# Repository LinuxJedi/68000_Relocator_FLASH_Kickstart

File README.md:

# 68000 Relocator with FLASH based Kickstart
Forked from https://github.com/PR77/68000_Relocator_FLASH_Kickstart and the software and firmware have been modified as well as a GUI tool created.

It now supports two flashed kickstart ROMs and has a cleaner interface.

**NOTE:** If you are using FK 3.0 command line tool or FlashKickstart GUI tool you will need to use the 3.0 Xilinx firmware too. Otherwise hi/lo ROMs will be the mapped to the same address.

**NOTE 2:** With firmware version 3.4 onwards the the jumper now switches between motherboard and ROM bank 1 as the first ROM. Jumper off for motherboard, jumper on for board ROM1. You will need 39SF040 ROM chips to use 3.4 onwards.

**NOTE 3:** The hardware directory in this tree was a PoC and will not work. Please use PR77's board linked to in the GitHub link above.

# Overview
To allow for Flash Kickstart images to be mapped in the same address space as existing ROM Kickstart without the need to remove the existing ROM. This design is targeting an accelerated A500(+) system which also require a CPU relocation.

# Flashing new ROMs
It is recommended you use the included FlashKickstart GUI tool. To use this you may need to install the reqtools library in your LIBS: drive. If you are using Kickstart 1.3 this is available in the lib13 directory of the software, for 2.0 onwards use the version in libs20 directory.

You can then load "FlashKickstart" and you should see the window similar to below:

You need to erase the ROMs before flashing a new image. Erasing will clear both the flash ROM slots.

You can then program with any ROM you wish. You should not use byte-swapped ROMs.

# Using the ROMs
In principle the operation is fairly simple. A CPLD is used to switch between the ROM Kickstart on the Motherboard or the two Flash Kickstart on the CPU Relocator. Switching is performed by an active /RESET (CTRL-A-A) without interruption for longer than 1 second. Shorter /RESET durations will simply just reset the Amiga. After a POR (Power On Reset) by default the Kickstart on the Motherboard will be used.

## ROM based Kickstart
When ROM Kickstart is being used, the hardware simply passed /AS to the Amiga Motherboard to allow GARY perform the address decode and chip select of the internal ROM. During this process, the Flash Kickstart is simply not used - except when programming. A Zorro II space of 1MB is requested and allocated by the Amiga which maps to the Flash devices.

When programming the Flash devices, access is via this Zorro II space. Programming of the Flash devices can only be performed when ROM Kickstart is being used.

## FLASH based Kickstart
When Flash Kickstart is being used, the hardware simply blocks /AS to the Amiga Motherboard and the CPLD will perform the operation of Flash device control. As /AS is not asserted on the Amiga Motherboard, and therefore no GARY decode, the Relocator CPLD will then also assert the /DTACK after placing data on the bus - this is needed to complete the CPU cycle.

### Overlay Interception
When Flash Kickstart mode is being used, the CPLD will also intercept the overlay of the Kickstart in the 0x000000 memory space until the first access to the custom chip register is performed. This ensures the correct SP and IP initialisation is performed directly after POR (Power On Reset) as the Flash Kickstart is used by default.

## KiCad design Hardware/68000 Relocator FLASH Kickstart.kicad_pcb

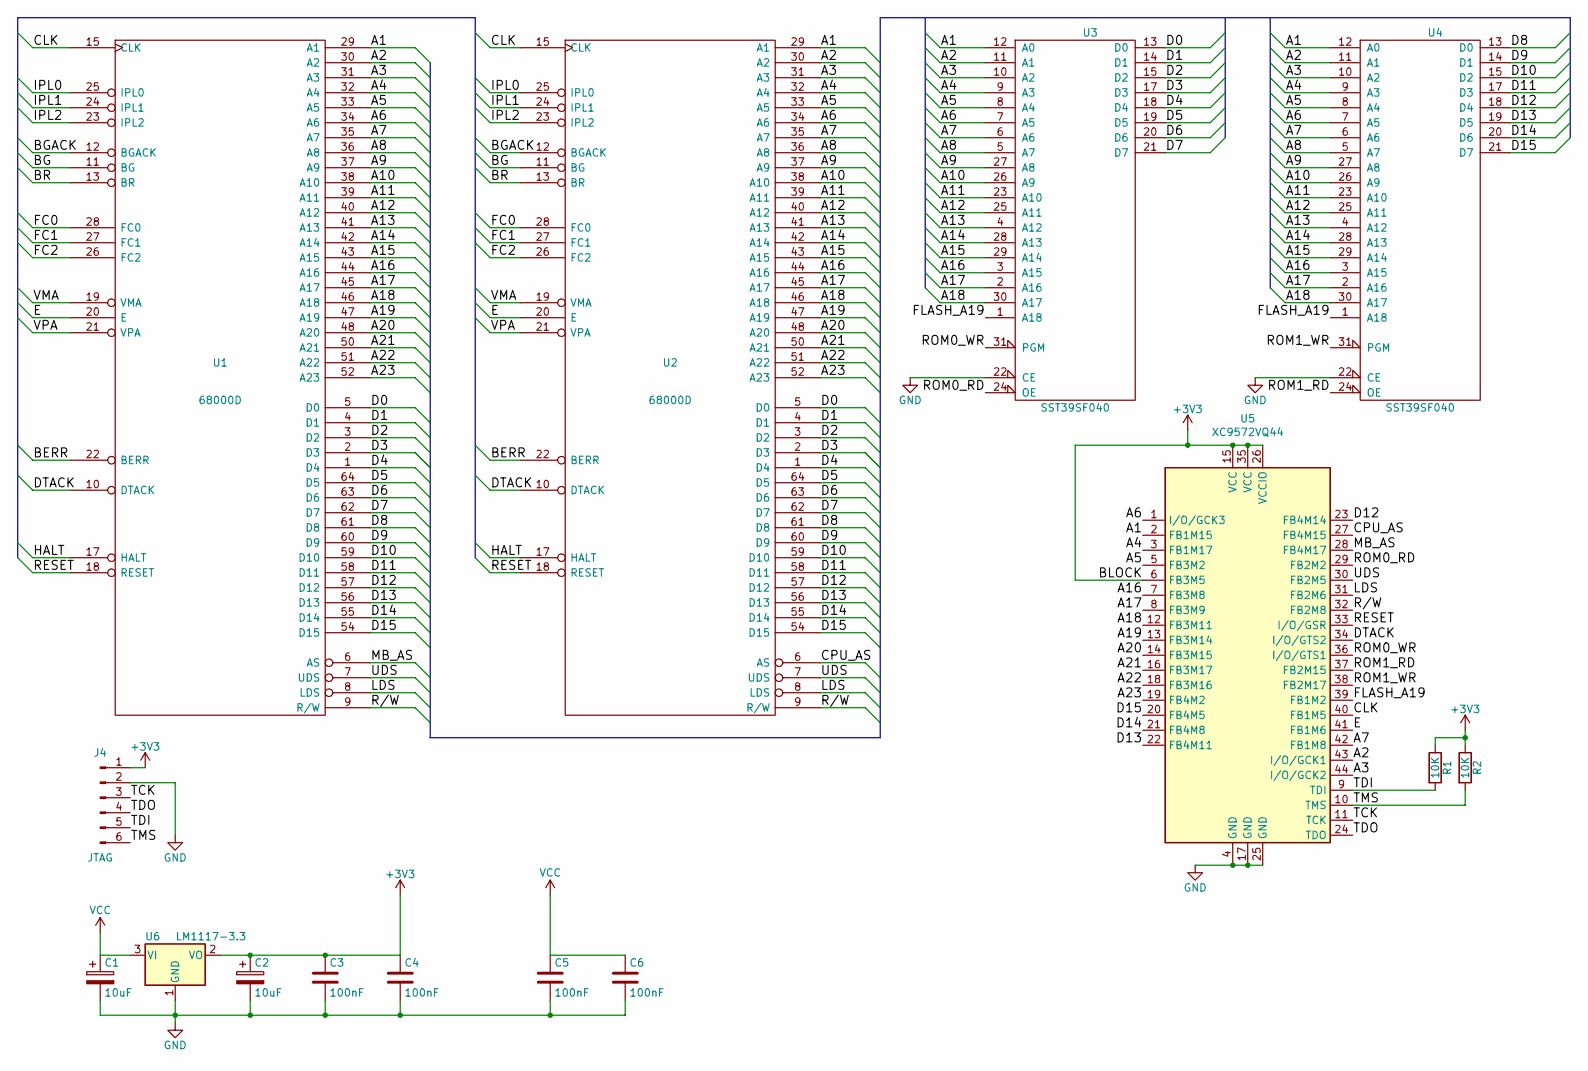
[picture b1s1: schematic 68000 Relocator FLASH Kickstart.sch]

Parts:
C1, C2: 10uF; CP_Tantalum_Case-B_EIA-3528-21_Hand
C3, C4, C5, C6: 100nF; C_0805_HandSoldering
J4: JTAG; Pin_Header_Straight_1x06_Pitch2.54mm
R1, R2: 10K; R_0805_HandSoldering
U1, U2: 68000D; DIP-64_W22.86mm_Socket_LongPads
U3, U4: SST39SF040; DIP-32_W15.24mm_Socket
U5: XC9572VQ44; TQFP-44_10x10mm_Pitch0.8mm
U6: LM1117-3.3; SOT-223-3_TabPin2

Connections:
+3V3: C2.1, C3.1, C4.1, J4.1, R1.1, R2.1, U5.6 (FB3M5), U5.15 (VCC), U5.26 (VCCIO), U5.35 (VCC), U6.2 (VO)
/A1: U1.29 (A1), U2.29 (A1), U3.12 (A0), U4.12 (A0), U5.2 (FB1M15)
/A2: U1.30 (A2), U2.30 (A2), U3.11 (A1), U4.11 (A1), U5.43 (I/O/GCK1)
/A3: U1.31 (A3), U2.31 (A3), U3.10 (A2), U4.10 (A2), U5.44 (I/O/GCK2)
/A4: U1.32 (A4), U2.32 (A4), U3.9 (A3), U4.9 (A3), U5.3 (FB1M17)
/A5: U1.33 (A5), U2.33 (A5), U3.8 (A4), U4.8 (A4), U5.5 (FB3M2)
/A6: U1.34 (A6), U2.34 (A6), U3.7 (A5), U4.7 (A5), U5.1 (I/O/GCK3)
/A7: U1.35 (A7), U2.35 (A7), U3.6 (A6), U4.6 (A6), U5.42 (FB1M8)
/A8: U1.36 (A8), U2.36 (A8), U3.5 (A7), U4.5 (A7)
/A9: U1.37 (A9), U2.37 (A9), U3.27 (A8), U4.27 (A8)
/A10: U1.38 (A10), U2.38 (A10), U3.26 (A9), U4.26 (A9)
/A11: U1.39 (A11), U2.39 (A11), U3.23 (A10), U4.23 (A10)
/A12: U1.40 (A12), U2.40 (A12), U3.25 (A11), U4.25 (A11)
/A13: U1.41 (A13), U2.41 (A13), U3.4 (A12), U4.4 (A12)
/A14: U1.42 (A14), U2.42 (A14), U3.28 (A13), U4.28 (A13)
/A15: U1.43 (A15), U2.43 (A15), U3.29 (A14), U4.29 (A14)
/A16: U1.44 (A16), U2.44 (A16), U3.3 (A15), U4.3 (A15), U5.7 (FB3M8)
/A17: U1.45 (A17), U2.45 (A17), U3.2 (A16), U4.2 (A16), U5.8 (FB3M9)
/A18: U1.46 (A18), U2.46 (A18), U3.30 (A17), U4.30 (A17), U5.12 (FB3M11)
/A19: U1.47 (A19), U2.47 (A19), U5.13 (FB3M14)
/A20: U1.48 (A20), U2.48 (A20), U5.14 (FB3M15)
/A21: U1.50 (A21), U2.50 (A21), U5.16 (FB3M17)
/A22: U1.51 (A22), U2.51 (A22), U5.18 (FB3M16)
/A23: U1.52 (A23), U2.52 (A23), U5.19 (FB4M2)
/BERR: U1.22 (BERR), U2.22 (BERR)
/BG: U1.11 (BG), U2.11 (BG)
/BGACK: U1.12 (BGACK), U2.12 (BGACK)
/BR: U1.13 (BR), U2.13 (BR)
/CLK: U1.15 (CLK), U2.15 (CLK), U5.40 (FB1M5)
/CPU_AS: U2.6 (AS), U5.27 (FB4M15)
/D0: U1.5 (D0), U2.5 (D0), U3.13 (D0)
/D1: U1.4 (D1), U2.4 (D1), U3.14 (D1)
/D2: U1.3 (D2), U2.3 (D2), U3.15 (D2)
/D3: U1.2 (D3), U2.2 (D3), U3.17 (D3)
/D4: U1.1 (D4), U2.1 (D4), U3.18 (D4)
/D5: U1.64 (D5), U2.64 (D5), U3.19 (D5)
/D6: U1.63 (D6), U2.63 (D6), U3.20 (D6)
/D7: U1.62 (D7), U2.62 (D7), U3.21 (D7)
/D8: U1.61 (D8), U2.61 (D8), U4.13 (D0)
/D9: U1.60 (D9), U2.60 (D9), U4.14 (D1)
/D10: U1.59 (D10), U2.59 (D10), U4.15 (D2)
/D11: U1.58 (D11), U2.58 (D11), U4.17 (D3)
/D12: U1.57 (D12), U2.57 (D12), U4.18 (D4), U5.23 (FB4M14)
/D13: U1.56 (D13), U2.56 (D13), U4.19 (D5), U5.22 (FB4M11)
/D14: U1.55 (D14), U2.55 (D14), U4.20 (D6), U5.21 (FB4M8)
/D15: U1.54 (D15), U2.54 (D15), U4.21 (D7), U5.20 (FB4M5)
/DTACK: U1.10 (DTACK), U2.10 (DTACK), U5.34 (I/O/GTS2)
/E: U1.20 (E), U2.20 (E), U5.41 (FB1M6)
/FC0: U1.28 (FC0), U2.28 (FC0)
/FC1: U1.27 (FC1), U2.27 (FC1)
/FC2: U1.26 (FC2), U2.26 (FC2)
/FLASH_A19: U3.1 (A18), U4.1 (A18), U5.39 (FB1M2)
/HALT: U1.17 (HALT), U2.17 (HALT)
/IPL0: U1.25 (IPL0), U2.25 (IPL0)
/IPL1: U1.24 (IPL1), U2.24 (IPL1)
/IPL2: U1.23 (IPL2), U2.23 (IPL2)
/LDS: U1.8 (LDS), U2.8 (LDS), U5.31 (FB2M6)
/MB_AS: U1.6 (AS), U5.28 (FB4M17)
/R/W: U1.9 (R/W), U2.9 (R/W), U5.32 (FB2M8)
/RESET: U1.18 (RESET), U2.18 (RESET), U5.33 (I/O/GSR)
/ROM0_RD: U3.24 (OE), U5.29 (FB2M2)
/ROM0_WR: U3.31 (PGM), U5.36 (I/O/GTS1)
/ROM1_RD: U4.24 (OE), U5.37 (FB2M15)
/ROM1_WR: U4.31 (PGM), U5.38 (FB2M17)
/TCK: J4.3, U5.11 (TCK)
/TDI: J4.5, R1.2, U5.9 (TDI)
/TDO: J4.4, U5.24 (TDO)
/TMS: J4.6, R2.2, U5.10 (TMS)
/UDS: U1.7 (UDS), U2.7 (UDS), U5.30 (FB2M5)
/VMA: U1.19 (VMA), U2.19 (VMA)
/VPA: U1.21 (VPA), U2.21 (VPA)
GND: C1.2, C2.2, C3.2, C4.2, C5.2, C6.2, J4.2, U1.16 (GND), U1.53 (GND), U2.16 (GND), U2.53 (GND), U3.16 (GND), U3.22 (CE), U4.16 (GND), U4.22 (CE), U5.4 (GND), U5.17 (GND), U5.25 (GND), U6.1 (GND)
VCC: C1.1, C5.1, C6.1, U1.14 (VCC), U1.49 (VCC), U2.14 (VCC), U2.49 (VCC), U3.32 (VCC), U4.32 (VCC), U6.3 (VI)

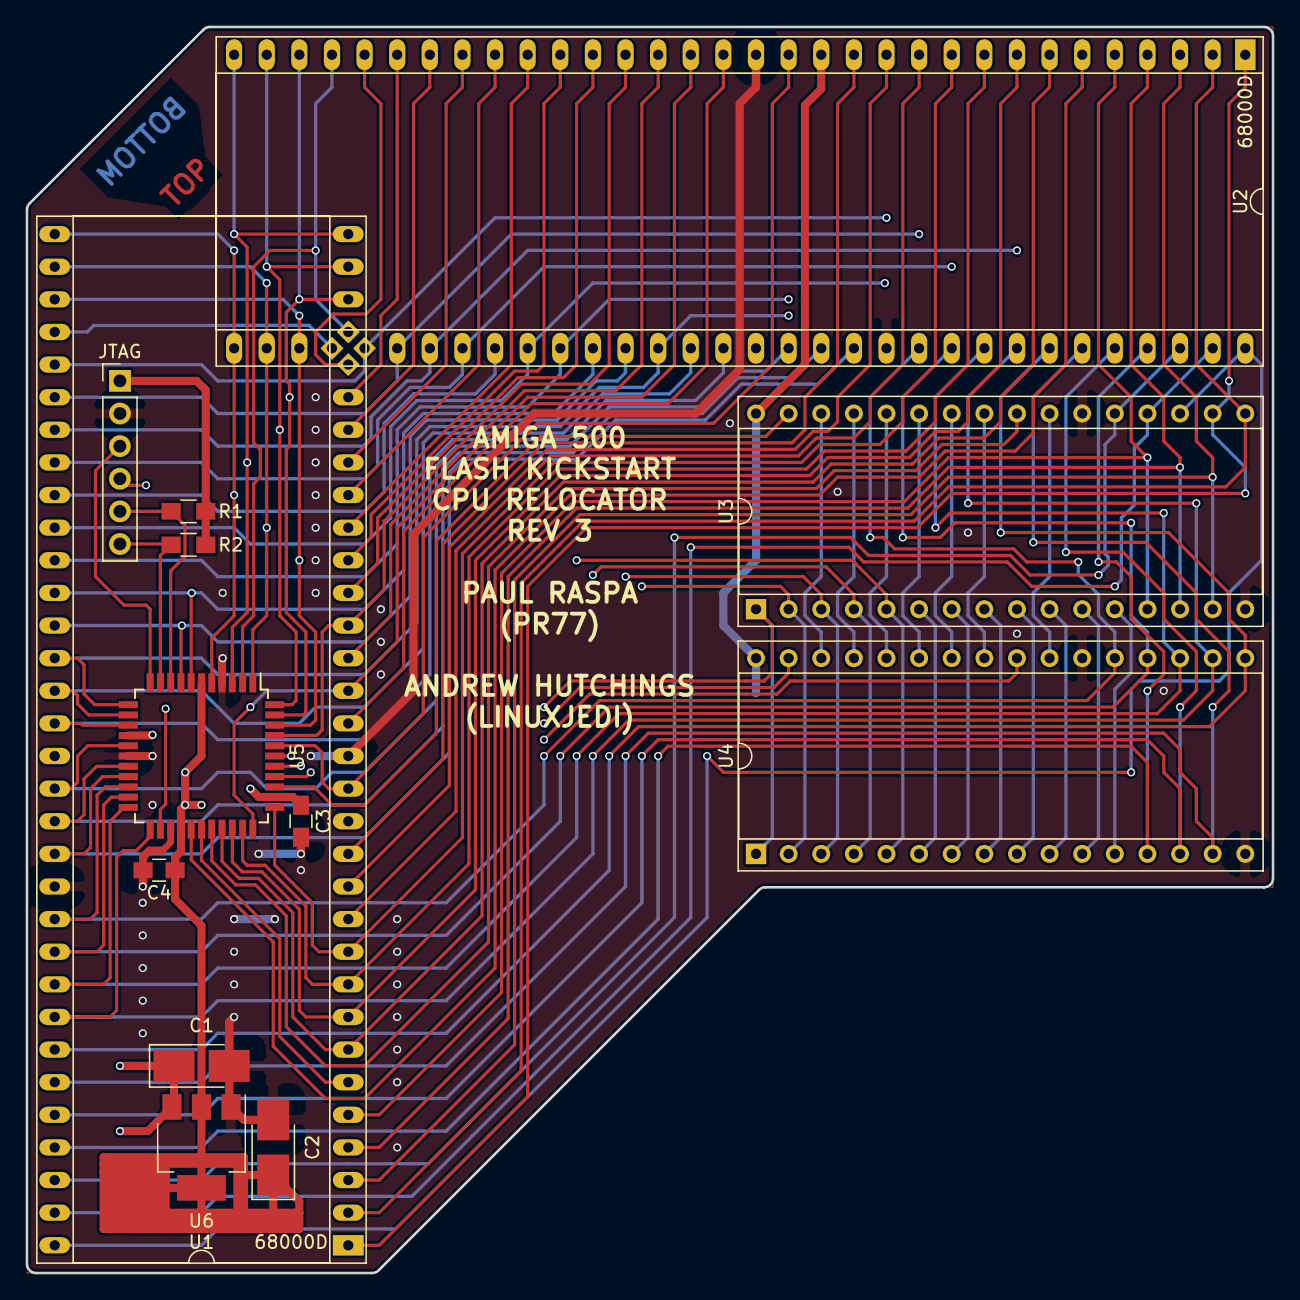
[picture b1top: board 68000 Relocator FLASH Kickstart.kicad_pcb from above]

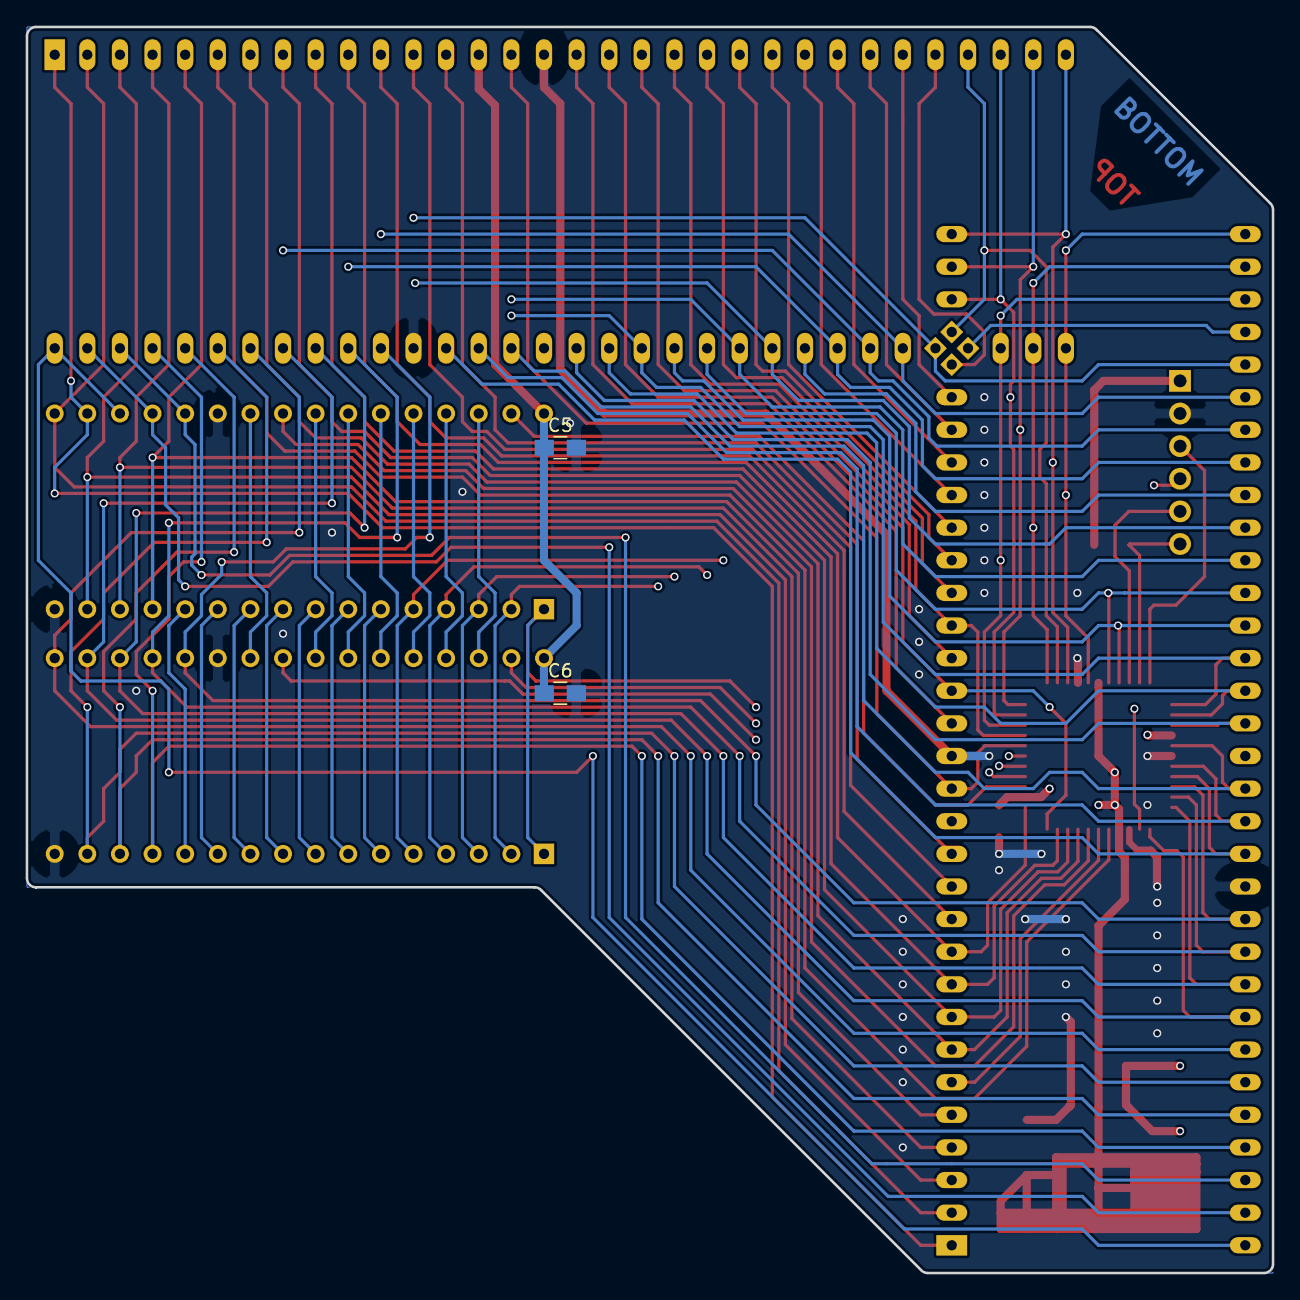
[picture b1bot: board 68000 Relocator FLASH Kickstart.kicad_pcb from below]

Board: 4 copper layers, 97.0 x 97.0 mm, 15 parts (2 on the bottom side), 73 nets.

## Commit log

2021-02-13 Add missing license header
2021-02-15 V 1.1 of GUI and Rev 3 PCB
    GUI:
    * No longer requires entire ROM to be flashed to be loaded into RAM
    PCB:
    * Removed tick
    * Made PCB a little smaller
    * Removed unneeded jumper
2021-02-24 Modify FK command line tool to use less RAM
2021-02-24 Switch to VBCC
    GCC compilation was causing a weird issue where when starting the GUI
    by double-clicking the icon in WB 1.3 the entire system would
    immediately crash hard. But it worked fine when executing from a shell.
    Switched to VBCC which appears to have solved the problem. Also some
    minor code cleanups.
2021-02-24 Version 1.3
    * Add info files for libs dirs
    * Auto-fallback to loading lib from floppy disk
    * Add scripts to create ADF and LHA
2021-02-24 Add script comments
2021-02-25 Critical bug fixes
    1. Turns out VBCC does maths a little differently and ROM2 reading was
    completely broken for both CLI and GUI
    2. Turns out KS1.3 is really picky on path formation, so fix that
2021-02-27 Add Verilog build script
2021-03-05 Cleanups and new features
    Logic:
    * Make the autoconfig easier to read
    * Add versioning as the serial to the autoconfig
    CLI:
    * Show board version number in information
    GUI:
2021-03-10 Board can work outside the 8MB Zorro II range
    Toggle the bit to do this
2021-04-05 Fix 256K ROM flashing
    256K ROMs were not flashing correctly. We need to essentially double
    flash them low/hi.
2021-04-06 Reboot loop and software fixes
    Changes:
    * Fixed reboot loop on ROM2 in some scenarios
    * Ported 256K ROM fixes to CLI tool
    * Don't double-flash the 256K ROMs if the first flash fails
    * Make erase-before-flash more human
    * Remove error message that asked if you erased (since it is automatic)
2021-04-09 Accidentally commited a custom build
    It was booting ROM1 first.
2021-04-09 Update ROM version information
    Thanks to Pete Biggs who supplied information on ROM versions I was not
    aware of. The RomInfo code has been updated appropriately.
2021-04-21 Fixes from PiStorm testing
    Firmware
    * Jumper now determines which ROM will boot first (off for Motherboard).
    Firmware now only works with two-ROMs
    * Fix issue where held reset on first boot switches ROM (PiStorm boot)
    GUI Software
    * If autoconfig failed then disable ROM flashing with appropriate
2021-04-22 Add back firmware version history
2021-05-14 Add Amiga OS 3.2 support
2021-05-30 Fix font issues in GUI
    OS3.9 and others don't always use Topaz 8 as the default font. So fix
    the font to use Topaz 8 so that we don't break rendering.
    Fixes #12
